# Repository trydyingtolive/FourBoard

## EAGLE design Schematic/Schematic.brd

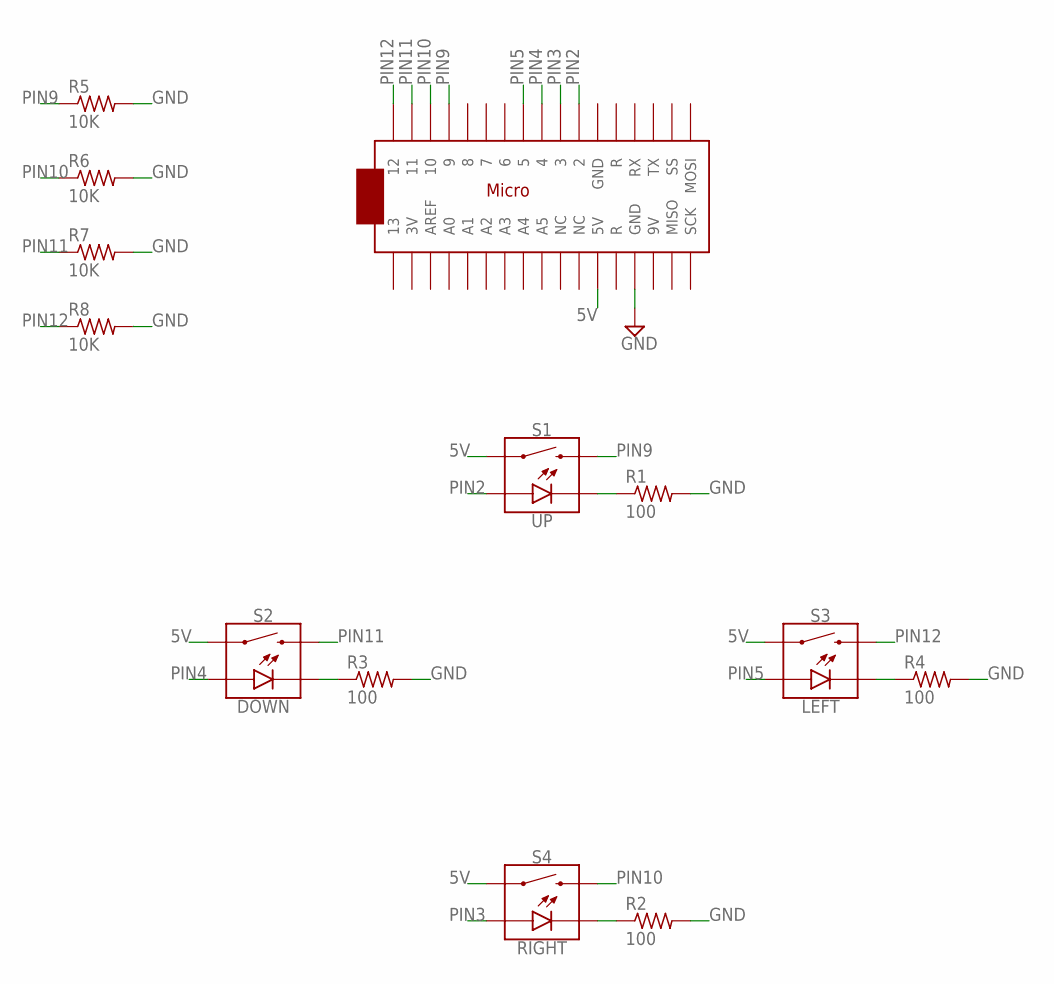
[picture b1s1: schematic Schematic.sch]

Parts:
R1, R2, R3, R4: 100; 0207/7
R5, R6, R7, R8: 10K; 0207/7
S1: UP; TACTILE_SWITCH_LED_PTH_12MM_KIT
S2: DOWN; TACTILE_SWITCH_LED_PTH_12MM_KIT
S3: LEFT; TACTILE_SWITCH_LED_PTH_12MM_KIT
S4: RIGHT; TACTILE_SWITCH_LED_PTH_12MM_KIT
U$1: ARDUINOMICRO

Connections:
5V: S1.4 (1), S2.4 (1), S3.4 (1), S4.4 (1), U$1.P$23 (5V)
GND: R1.2, R2.2, R3.2, R4.2, R5.2, R6.2, R7.2, R8.2, U$1.P$12 (GND)
unnamed: R1.1, S1.C
unnamed: R3.1, S2.C
unnamed: R2.1, S4.C
unnamed: R4.1, S3.C
PIN2: S1.A, U$1.P$11 (2)
PIN3: S4.A, U$1.P$10 (3)
PIN4: S2.A, U$1.P$9 (4)
PIN5: S3.A, U$1.P$8 (5)
PIN9: R5.1, S1.2, U$1.P$4 (9)
PIN10: R6.1, S4.2, U$1.P$3 (10)
PIN11: R7.1, S2.2, U$1.P$2 (11)
PIN12: R8.1, S3.2, U$1.P$1 (12)

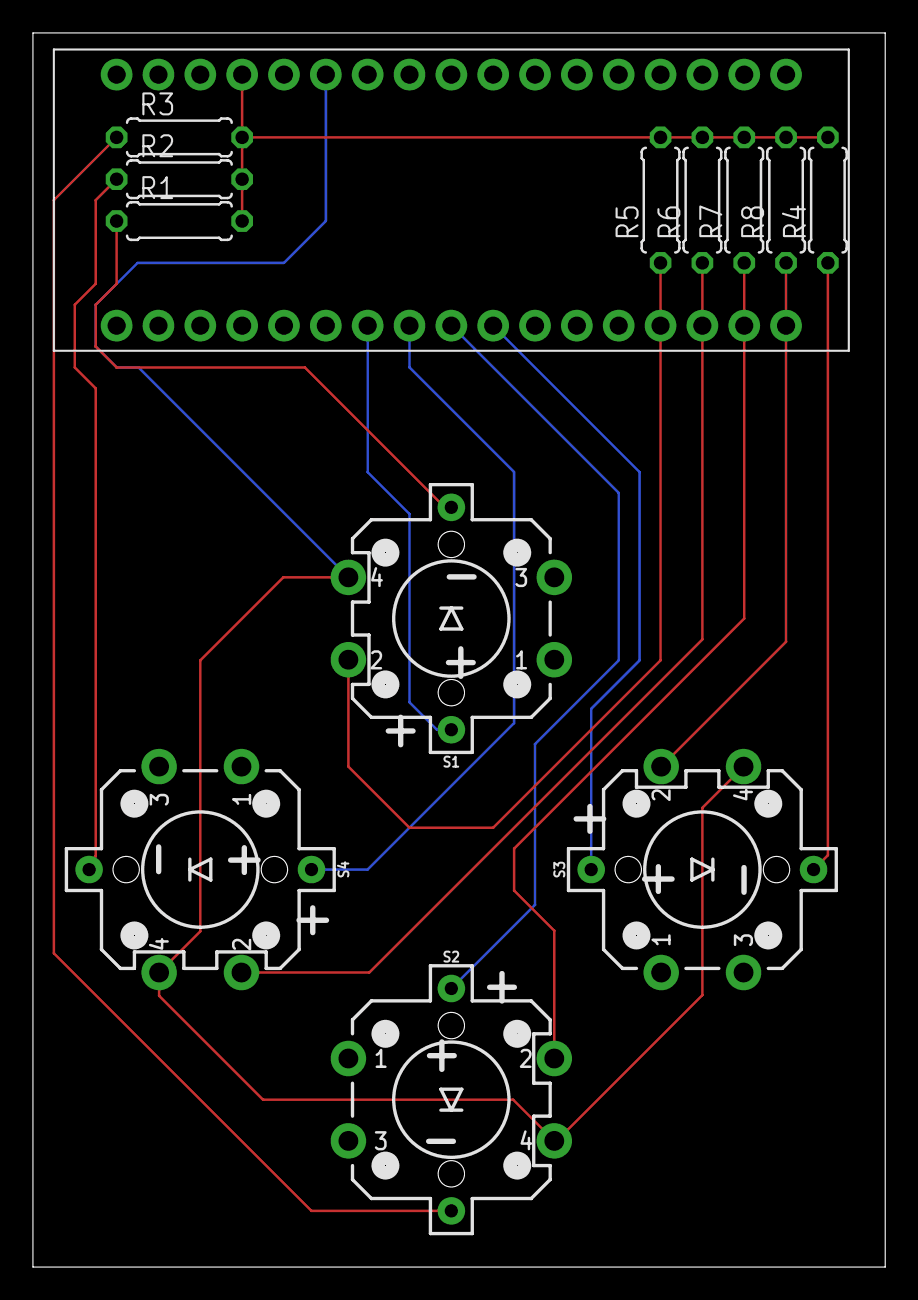
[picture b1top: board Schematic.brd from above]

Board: 2 copper layers, 51.7 x 74.9 mm, 13 parts (0 on the bottom side), 14 nets.

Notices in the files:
parts and their libraries:
SparkFun-Switches: Licensing: Creative Commons ShareAlike 4.0 International - https://creativecommons.org/licenses/by-sa/4.0
